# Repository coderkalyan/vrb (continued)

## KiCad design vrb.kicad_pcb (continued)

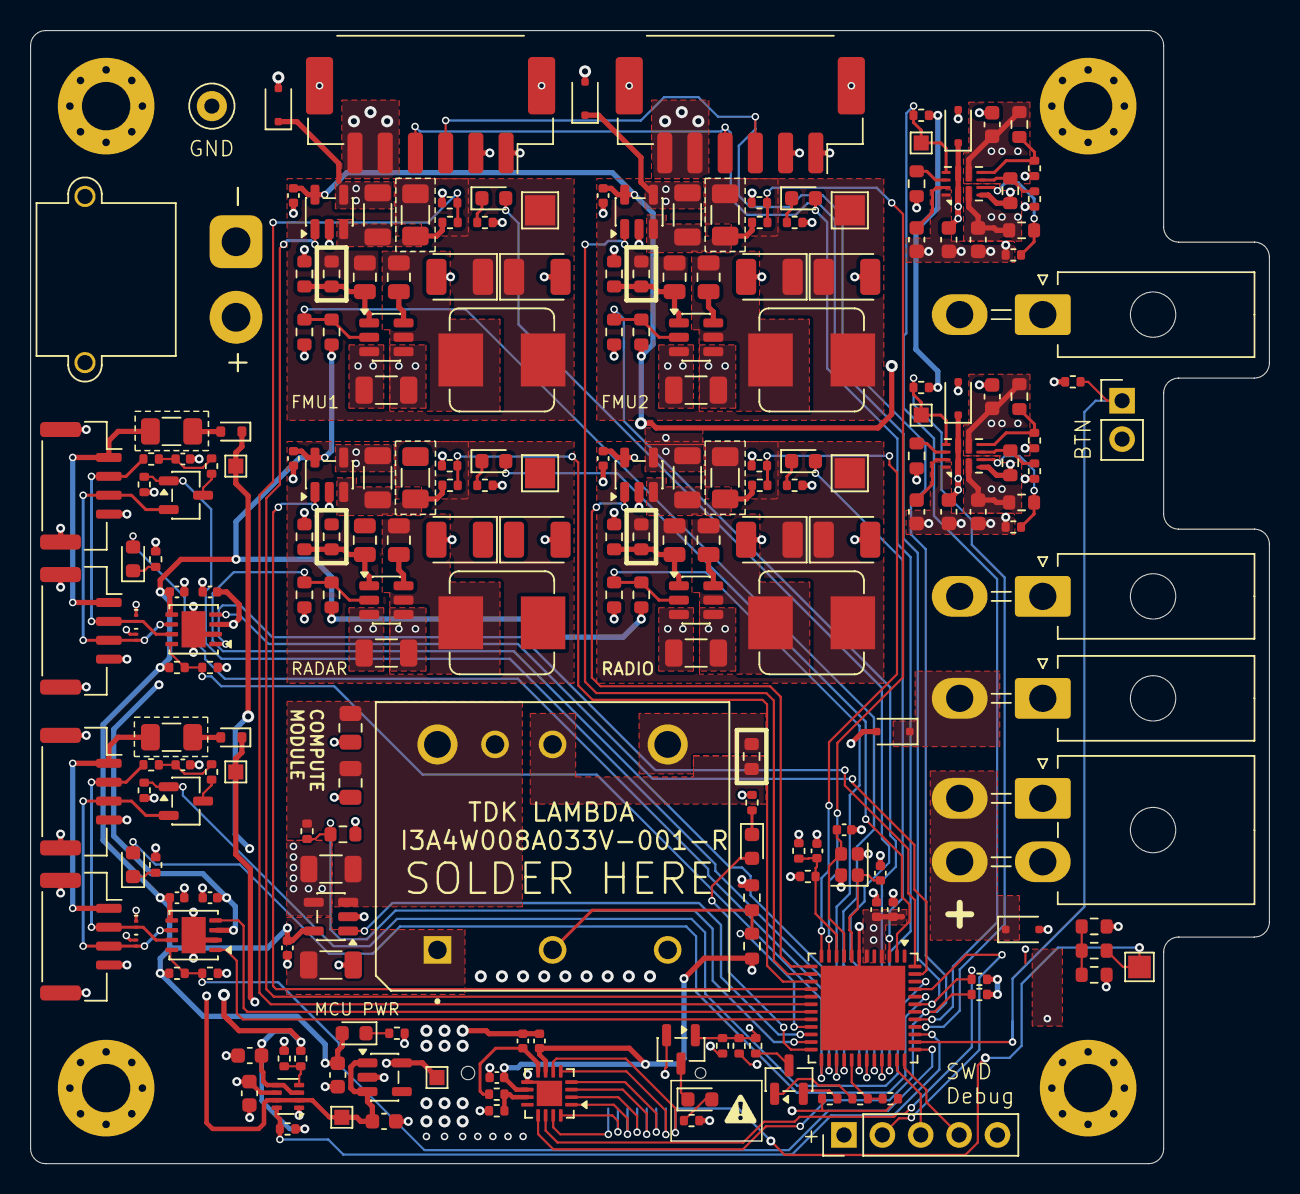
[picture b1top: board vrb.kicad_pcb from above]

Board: 6 copper layers, 82.0 x 75.0 mm, 226 parts (1 on the bottom side), 126 nets.

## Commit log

2025-12-28 work on layout
2025-12-30 finish layout
2025-12-30 move to 6 layer
2025-12-30 optimize components, update schematic pdf
2026-01-07 added silk screen stuff
2026-01-11 improvements with derick
2026-01-12 final export of r1 after changes
2026-01-21 created new fault circuitry and assignemd compoennts, need to perform layout
2026-02-03 updated layout for fault led with new circuit, rerouted
